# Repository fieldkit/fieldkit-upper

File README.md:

# FieldKit-*Upper*
The Upper board constitutes the thinky bits of the FieldKit system.

## Architecture
Every Fieldkit has at least three boards: Upper, Lower, and Module Base. Upper contains :

- The microcontroller.
- The OLED display and buttons.
- The real-time clock and its backup power supply.
- Flash memory for firmware.
- Separate NAND flash for data storage.
- The Micro-SD Card Slot.
- The USB Port.
- A temperature sensor.

## License Information

> *"In the long history of humankind (and animal kind, too) those who learned to collaborate and improvise most effectively have prevailed."*
>  --**Charles Darwin**

This hardware is released under **CERN Open Hardware License Version 2 - Permissive (CERN-OHL_P)**
Obviously, it's Distributed as-is; and no warranty is given.

---
*Upper was Designed by Bradley Gawthrop for FieldKit.*

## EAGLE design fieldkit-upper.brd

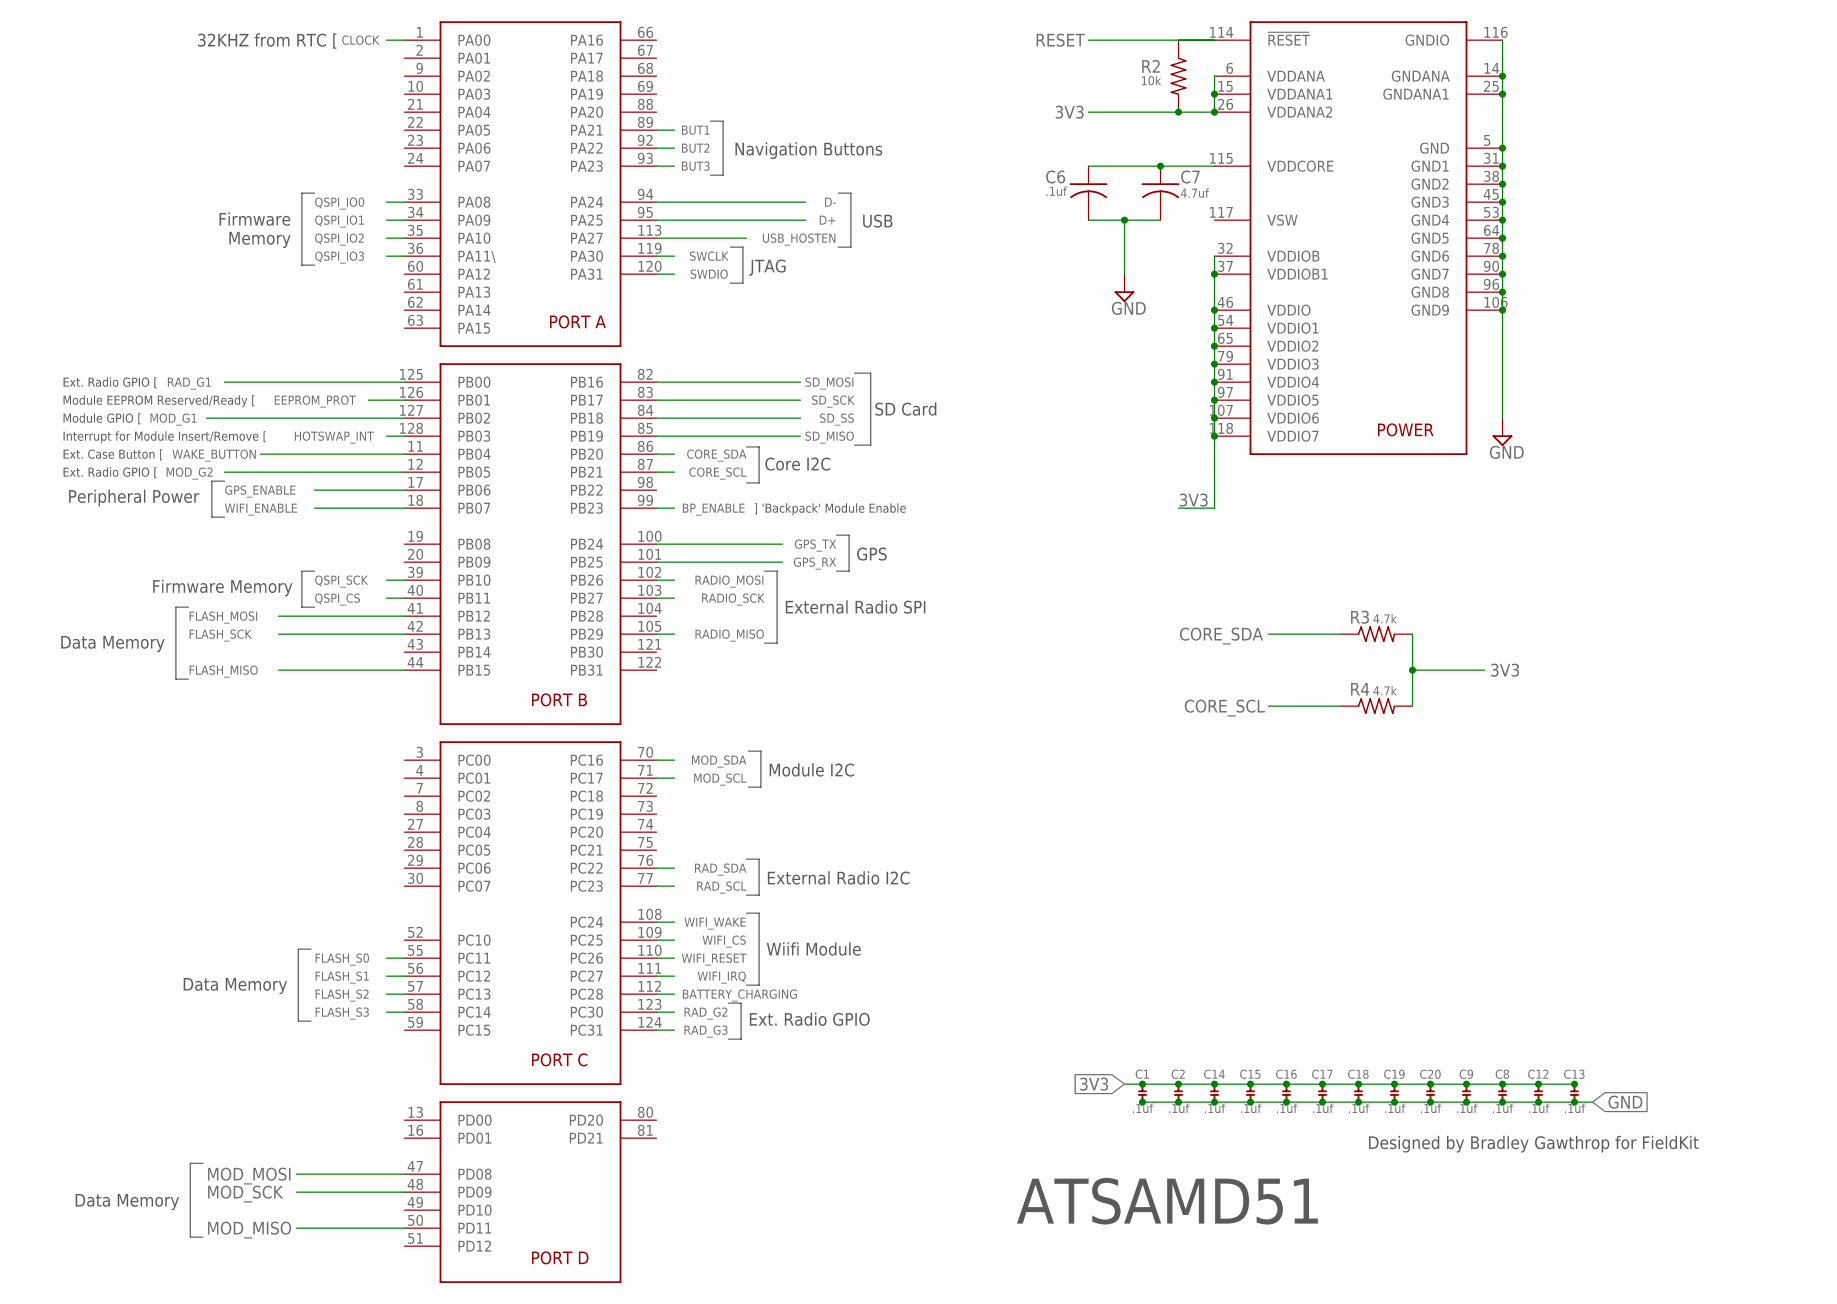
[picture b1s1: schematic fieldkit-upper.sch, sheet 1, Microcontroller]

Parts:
BRAIN: SAMD51PXXA; SQFP-S-14X14-128
C1, C2, C6, C8, C9, C12, C13, C14, C15, C16, C17, C18, C19, C20: .1uf; C0603K
C7: 4.7uf; C0603K
R2: 10k; R0603
R3, R4: 4.7k; R0603

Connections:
3V3: BRAIN.6 (VDDANA), BRAIN.15 (VDDANA1), BRAIN.26 (VDDANA2), BRAIN.32 (VDDIOB), BRAIN.37 (VDDIOB1), BRAIN.46 (VDDIO), BRAIN.54 (VDDIO1), BRAIN.65 (VDDIO2), BRAIN.79 (VDDIO3), BRAIN.91 (VDDIO4), BRAIN.97 (VDDIO5), BRAIN.107 (VDDIO6), BRAIN.118 (VDDIO7), C1.1, C2.1, C8.1, C9.1, C12.1, C13.1, C14.1, C15.1, C16.1, C17.1, C18.1, C19.1, C20.1, R2.2, R3.2, R4.2; also elsewhere on the board
BATTERY_CHARGING: BRAIN.112 (PC28); also elsewhere on the board
BP_ENABLE: BRAIN.99 (PB23); also elsewhere on the board
BUT1: BRAIN.89 (PA21); also elsewhere on the board
BUT2: BRAIN.92 (PA22); also elsewhere on the board
BUT3: BRAIN.93 (PA23); also elsewhere on the board
CLOCK: BRAIN.1 (PA00); also elsewhere on the board
CORE_SCL: BRAIN.87 (PB21), R4.1; also elsewhere on the board
CORE_SDA: BRAIN.86 (PB20), R3.1; also elsewhere on the board
D+: BRAIN.95 (PA25); also elsewhere on the board
D-: BRAIN.94 (PA24); also elsewhere on the board
EEPROM_PROT: BRAIN.126 (PB01); also elsewhere on the board
FLASH_MISO: BRAIN.44 (PB15); also elsewhere on the board
FLASH_MOSI: BRAIN.41 (PB12); also elsewhere on the board
FLASH_S0: BRAIN.55 (PC11); also elsewhere on the board
FLASH_S1: BRAIN.56 (PC12); also elsewhere on the board
FLASH_S2: BRAIN.57 (PC13); also elsewhere on the board
FLASH_S3: BRAIN.58 (PC14); also elsewhere on the board
FLASH_SCK: BRAIN.42 (PB13); also elsewhere on the board
GND: BRAIN.5 (GND), BRAIN.14 (GNDANA), BRAIN.25 (GNDANA1), BRAIN.31 (GND1), BRAIN.38 (GND2), BRAIN.45 (GND3), BRAIN.53 (GND4), BRAIN.64 (GND5), BRAIN.78 (GND6), BRAIN.90 (GND7), BRAIN.96 (GND8), BRAIN.106 (GND9), BRAIN.116 (GNDIO), C1.2, C2.2, C6.2, C7.2, C8.2, C9.2, C12.2, C13.2, C14.2, C15.2, C16.2, C17.2, C18.2, C19.2, C20.2; also elsewhere on the board
GPS_ENABLE: BRAIN.17 (PB06); also elsewhere on the board
GPS_RX: BRAIN.101 (PB25); also elsewhere on the board
GPS_TX: BRAIN.100 (PB24); also elsewhere on the board
HOTSWAP_INT: BRAIN.128 (PB03); also elsewhere on the board
MOD_G1: BRAIN.127 (PB02); also elsewhere on the board
MOD_G2: BRAIN.12 (PB05)
MOD_MISO: BRAIN.50 (PD11); also elsewhere on the board
MOD_MOSI: BRAIN.47 (PD08); also elsewhere on the board
MOD_SCK: BRAIN.48 (PD09); also elsewhere on the board
MOD_SCL: BRAIN.71 (PC17); also elsewhere on the board
MOD_SDA: BRAIN.70 (PC16); also elsewhere on the board
unnamed: BRAIN.115 (VDDCORE), C6.1, C7.1
QSPI_CS: BRAIN.40 (PB11); also elsewhere on the board
QSPI_IO0: BRAIN.33 (PA08); also elsewhere on the board
QSPI_IO1: BRAIN.34 (PA09); also elsewhere on the board
QSPI_IO2: BRAIN.35 (PA10); also elsewhere on the board
QSPI_IO3: BRAIN.36 (PA11\); also elsewhere on the board
QSPI_SCK: BRAIN.39 (PB10); also elsewhere on the board
RADIO_MISO: BRAIN.105 (PB29); also elsewhere on the board
RADIO_MOSI: BRAIN.102 (PB26); also elsewhere on the board
RADIO_SCK: BRAIN.103 (PB27); also elsewhere on the board
RAD_G1: BRAIN.125 (PB00); also elsewhere on the board
RAD_G2: BRAIN.123 (PC30); also elsewhere on the board
RAD_G3: BRAIN.124 (PC31); also elsewhere on the board
RAD_SCL: BRAIN.77 (PC23); also elsewhere on the board
RAD_SDA: BRAIN.76 (PC22); also elsewhere on the board
RESET: BRAIN.114 (!RESET), R2.1; also elsewhere on the board
SD_MISO: BRAIN.85 (PB19); also elsewhere on the board
SD_MOSI: BRAIN.82 (PB16); also elsewhere on the board
SD_SCK: BRAIN.83 (PB17); also elsewhere on the board
SD_SS: BRAIN.84 (PB18); also elsewhere on the board
SWCLK: BRAIN.119 (PA30); also elsewhere on the board
SWDIO: BRAIN.120 (PA31); also elsewhere on the board
USB_HOSTEN: BRAIN.113 (PA27)
WAKE_BUTTON: BRAIN.11 (PB04); also elsewhere on the board
WIFI_CS: BRAIN.109 (PC25); also elsewhere on the board
WIFI_ENABLE: BRAIN.18 (PB07); also elsewhere on the board
WIFI_IRQ: BRAIN.111 (PC27); also elsewhere on the board
WIFI_RESET: BRAIN.110 (PC26); also elsewhere on the board
WIFI_WAKE: BRAIN.108 (PC24); also elsewhere on the board

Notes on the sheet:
Navigation Buttons
32KHZ from RTC [
Firmware Memory
USB
JTAG
SD Card
Core I2C
External Radio SPI
] 'Backpack' Module Enable
Data Memory
Firmware Memory
Module I2C
External Radio I2C
Interrupt for Module Insert/Remove [
GPS
Ext. Radio GPIO [
Module EEPROM Reserved/Ready [
Module GPIO [
Ext. Case Button [
Peripheral Power
Wiifi Module
Ext. Radio GPIO
ATSAMD51
Designed by Bradley Gawthrop for FieldKit

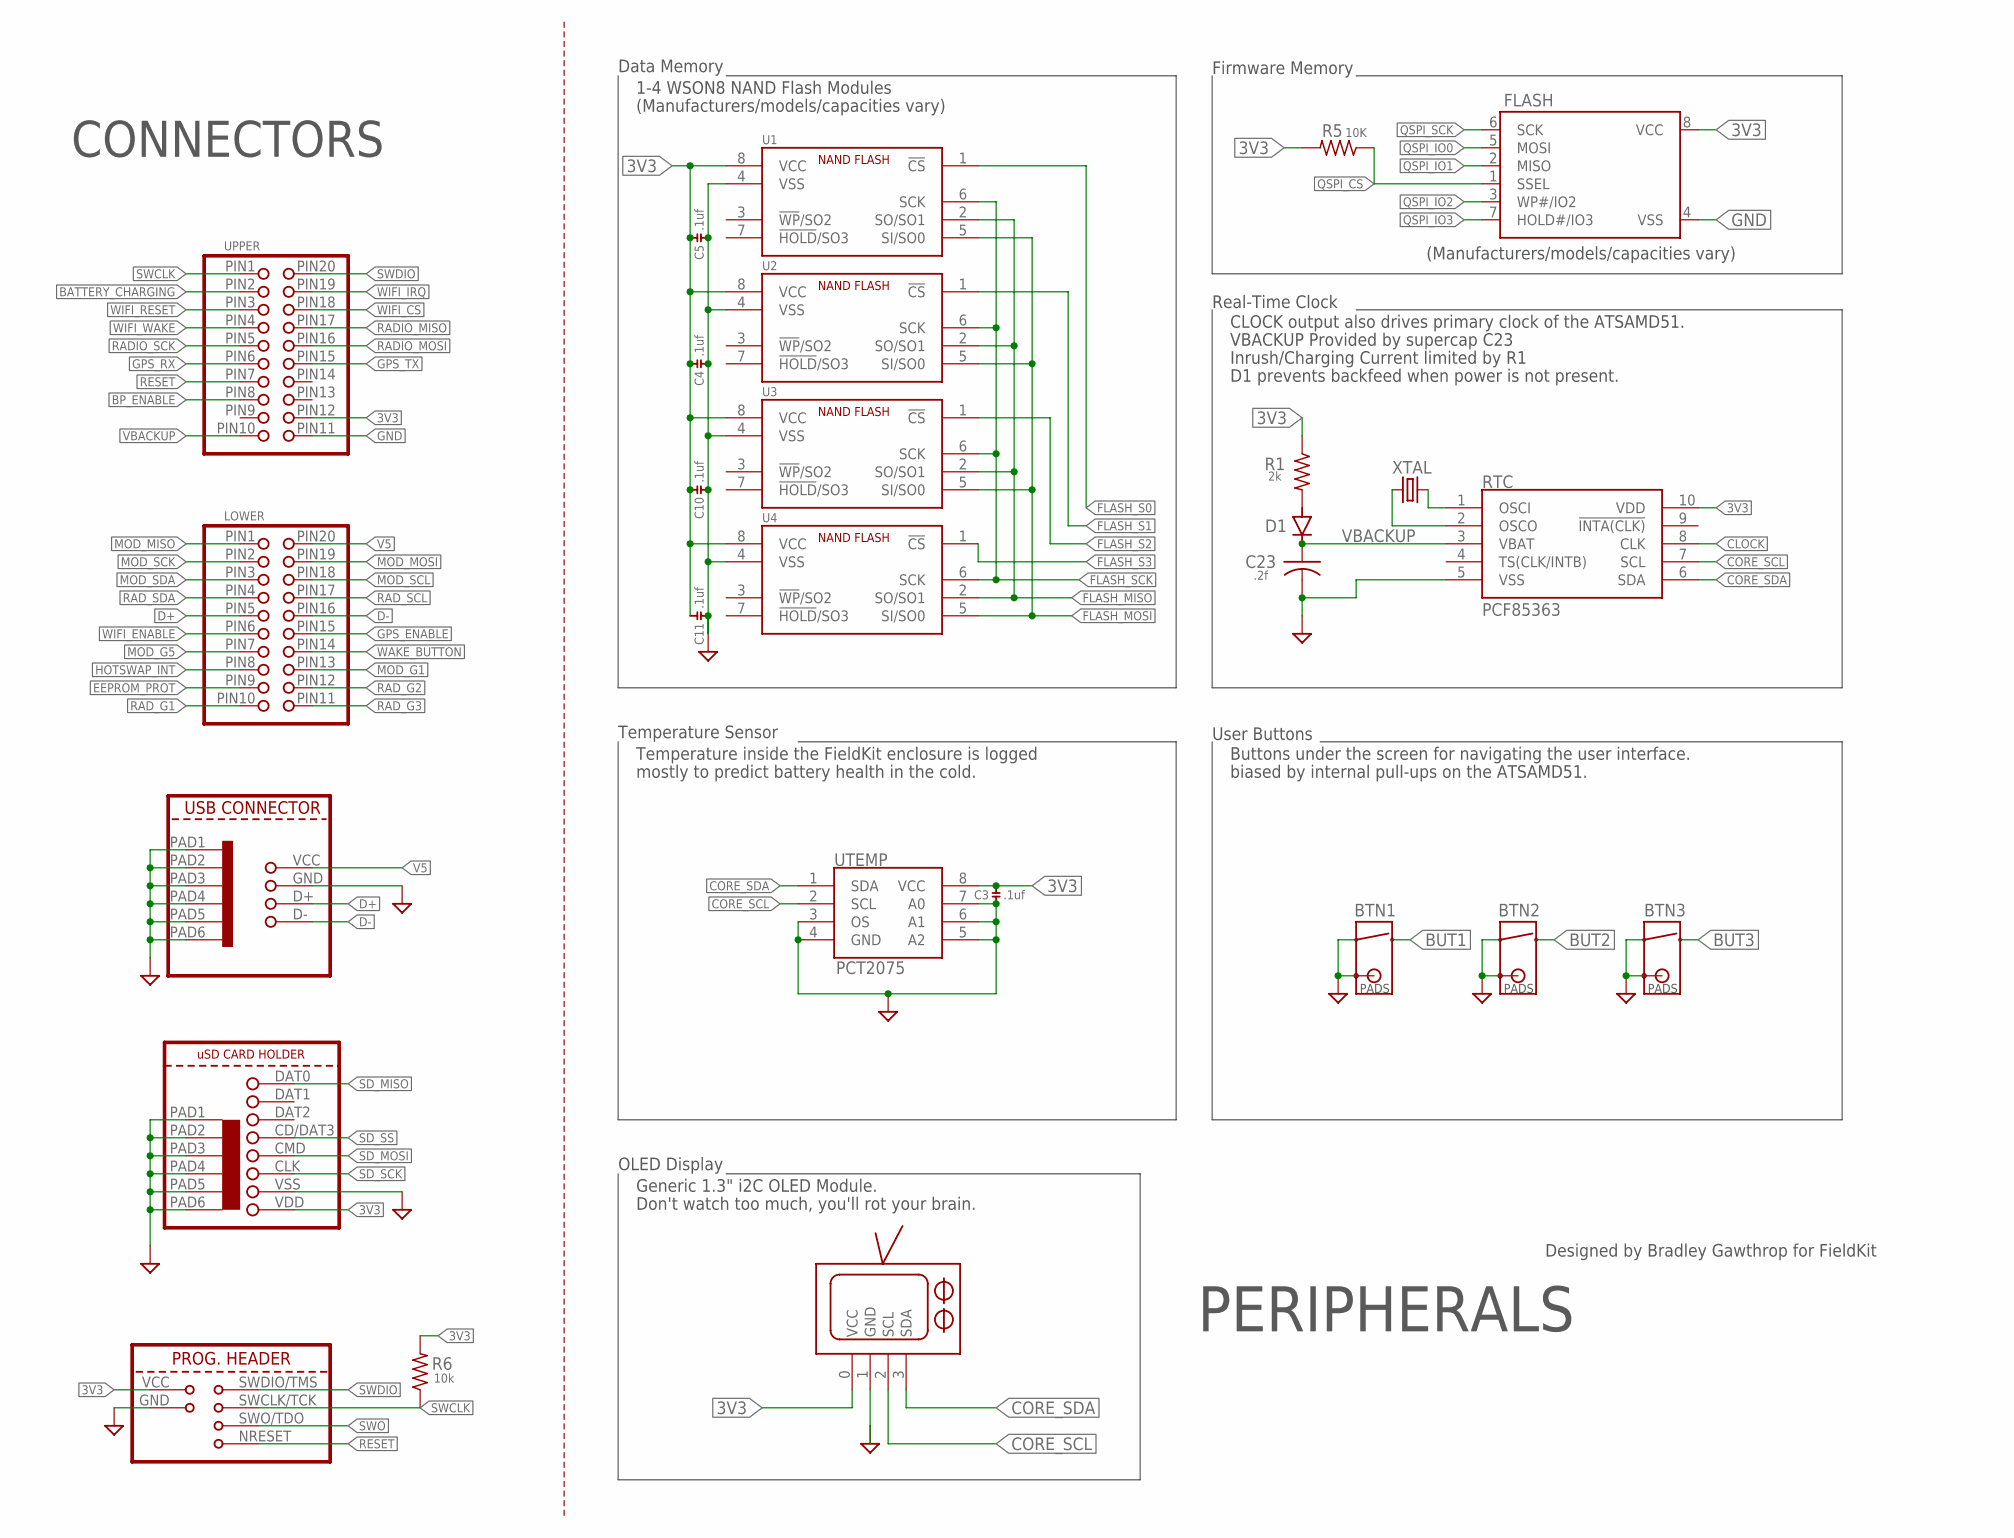
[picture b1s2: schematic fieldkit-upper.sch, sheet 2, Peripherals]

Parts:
BTN1, BTN2, BTN3: SKRTLAE010
C3, C4, C5, C10, C11: .1uf; C0603K
C23: .2f; SUPERCAP
D1: VS-10BQ015HM3/5BT; SMB
FLASH: SPIFLASH_SOIC8208MIL; SOIC8_208MIL
J1: TAG-CONNECT; TC2030-IDC
LOWER: MOLEX-15-91-2200F; 20PH-F
R1: 2k; R0603
R5: 10K; R0603
R6: 10k; R0603
RTC: PCF85363ATT; SOP50P490X110-10
SCREEN: SCREEN
SD: DM3D-SF
U1, U2, U3, U4: TC58CVG1S3HRAIG; WSON8
UPPER: MOLEX-15-91-2200F; 20PH-F
USB: MOLEX-47491-0001; MOELX-47491-0001
UTEMP: PCT2075; SO8
XTAL: ABS07W

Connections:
3V3: C3.1, C4.1, C5.1, C10.1, C11.1, FLASH.8 (VCC), J1.VCC, R1.1, R5.2, R6.2, RTC.10 (VDD), SCREEN.0 (VCC), SD.VDD, U1.8 (VCC), U2.8 (VCC), U3.8 (VCC), U4.8 (VCC), UPPER.PIN12, UTEMP.8 (VCC); also elsewhere on the board
BATTERY_CHARGING: UPPER.PIN2; also elsewhere on the board
BP_ENABLE: UPPER.PIN8; also elsewhere on the board
BUT1: BTN1.B (2); also elsewhere on the board
BUT2: BTN2.B (2); also elsewhere on the board
BUT3: BTN3.B (2); also elsewhere on the board
CLOCK: RTC.8 (CLK); also elsewhere on the board
CORE_SCL: RTC.7 (SCL), SCREEN.2 (SCL), UTEMP.2 (SCL); also elsewhere on the board
CORE_SDA: RTC.6 (SDA), SCREEN.3 (SDA), UTEMP.1 (SDA); also elsewhere on the board
D+: LOWER.PIN5, USB.D+; also elsewhere on the board
D-: LOWER.PIN16, USB.D-; also elsewhere on the board
EEPROM_PROT: LOWER.PIN9; also elsewhere on the board
FLASH_MISO: U1.2 (SO/SO1), U2.2 (SO/SO1), U3.2 (SO/SO1), U4.2 (SO/SO1); also elsewhere on the board
FLASH_MOSI: U1.5 (SI/SO0), U2.5 (SI/SO0), U3.5 (SI/SO0), U4.5 (SI/SO0); also elsewhere on the board
FLASH_S0: U1.1 (!CS); also elsewhere on the board
FLASH_S1: U2.1 (!CS); also elsewhere on the board
FLASH_S2: U3.1 (!CS); also elsewhere on the board
FLASH_S3: U4.1 (!CS); also elsewhere on the board
FLASH_SCK: U1.6 (SCK), U2.6 (SCK), U3.6 (SCK), U4.6 (SCK); also elsewhere on the board
GND: BTN1.A (1), BTN1.A2 (1), BTN1.TAB (PADS), BTN1.TAB2 (PADS), BTN2.A (1), BTN2.A2 (1), BTN2.TAB (PADS), BTN2.TAB2 (PADS), BTN3.A (1), BTN3.A2 (1), BTN3.TAB (PADS), BTN3.TAB2 (PADS), C3.2, C4.2, C5.2, C10.2, C11.2, C23.-, FLASH.4 (VSS), J1.GND, RTC.5 (VSS), SCREEN.1 (GND), SD.PAD1, SD.PAD2, SD.PAD3, SD.PAD4, SD.PAD5, SD.PAD6, SD.VSS, U1.4 (VSS), U2.4 (VSS), U3.4 (VSS), U4.4 (VSS), UPPER.PIN11, USB.GND, USB.PAD1, USB.PAD2, USB.PAD3, USB.PAD4, USB.PAD5, USB.PAD6, UTEMP.3 (OS), UTEMP.4 (GND), UTEMP.5 (A2), UTEMP.6 (A1), UTEMP.7 (A0); also elsewhere on the board
GPS_ENABLE: LOWER.PIN15; also elsewhere on the board
GPS_RX: UPPER.PIN6; also elsewhere on the board
GPS_TX: UPPER.PIN15; also elsewhere on the board
HOTSWAP_INT: LOWER.PIN8; also elsewhere on the board
MOD_G1: LOWER.PIN13; also elsewhere on the board
MOD_G5: LOWER.PIN7
MOD_MISO: LOWER.PIN1; also elsewhere on the board
MOD_MOSI: LOWER.PIN19; also elsewhere on the board
MOD_SCK: LOWER.PIN2; also elsewhere on the board
MOD_SCL: LOWER.PIN18; also elsewhere on the board
MOD_SDA: LOWER.PIN3; also elsewhere on the board
unnamed: D1.A, R1.2
unnamed: RTC.1 (OSCI), XTAL.P$2 (2)
unnamed: RTC.2 (OSCO), XTAL.P$1 (1)
QSPI_CS: FLASH.1 (SSEL), R5.1; also elsewhere on the board
QSPI_IO0: FLASH.5 (MOSI); also elsewhere on the board
QSPI_IO1: FLASH.2 (MISO); also elsewhere on the board
QSPI_IO2: FLASH.3 (WP#/IO2); also elsewhere on the board
QSPI_IO3: FLASH.7 (HOLD#/IO3); also elsewhere on the board
QSPI_SCK: FLASH.6 (SCK); also elsewhere on the board
RADIO_MISO: UPPER.PIN17; also elsewhere on the board
RADIO_MOSI: UPPER.PIN16; also elsewhere on the board
RADIO_SCK: UPPER.PIN5; also elsewhere on the board
RAD_G1: LOWER.PIN10; also elsewhere on the board
RAD_G2: LOWER.PIN12; also elsewhere on the board
RAD_G3: LOWER.PIN11; also elsewhere on the board
RAD_SCL: LOWER.PIN17; also elsewhere on the board
RAD_SDA: LOWER.PIN4; also elsewhere on the board
RESET: J1.NRESET (RESET), UPPER.PIN7; also elsewhere on the board
SD_MISO: SD.DAT0; also elsewhere on the board
SD_MOSI: SD.CMD; also elsewhere on the board
SD_SCK: SD.CLK; also elsewhere on the board
SD_SS: SD.CD/DAT3 (DAT3); also elsewhere on the board
SWCLK: J1.SWCLK/TCK (SWCLK), R6.1, UPPER.PIN1; also elsewhere on the board
SWDIO: J1.SWDIO/TMS (SWDIO), UPPER.PIN20; also elsewhere on the board
SWO: J1.SWO/TDO (SWO)
V5: LOWER.PIN20, USB.VCC (VBUS)
VBACKUP: C23.+, D1.C, RTC.3 (VBAT), UPPER.PIN10
WAKE_BUTTON: LOWER.PIN14; also elsewhere on the board
WIFI_CS: UPPER.PIN18; also elsewhere on the board
WIFI_ENABLE: LOWER.PIN6; also elsewhere on the board
WIFI_IRQ: UPPER.PIN19; also elsewhere on the board
WIFI_RESET: UPPER.PIN3; also elsewhere on the board
WIFI_WAKE: UPPER.PIN4; also elsewhere on the board

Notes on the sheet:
.2f
CONNECTORS
Data Memory
1-4 WSON8 NAND Flash Modules
(Manufacturers/models/capacities vary)
Firmware Memory
Real-Time Clock
CLOCK output also drives primary clock of the ATSAMD51.
VBACKUP Provided by supercap C23
Inrush/Charging Current limited by R1
D1 prevents backfeed when power is not present.
RTC
PCF85363
Temperature Sensor
Temperature inside the FieldKit enclosure is logged
mostly to predict battery health in the cold.
User Buttons
Buttons under the screen for navigating the user interface.
biased by internal pull-ups on the ATSAMD51.
OLED Display
Generic 1.3" i2C OLED Module.
Don't watch too much, you'll rot your brain.
PERIPHERALS
Designed by Bradley Gawthrop for FieldKit

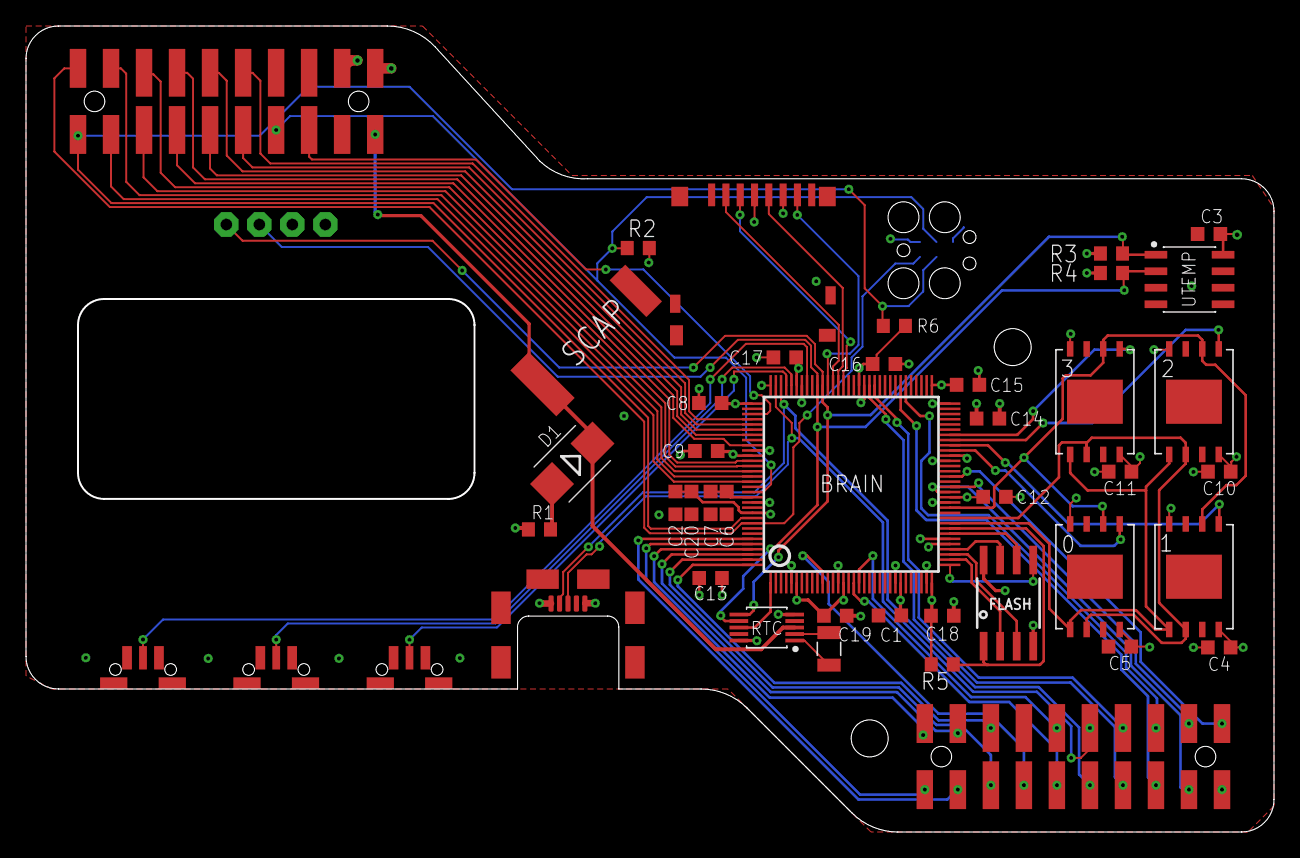
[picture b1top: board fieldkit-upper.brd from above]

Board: 4 copper layers, 95.8 x 61.8 mm, 46 parts (1 on the bottom side), 63 nets.

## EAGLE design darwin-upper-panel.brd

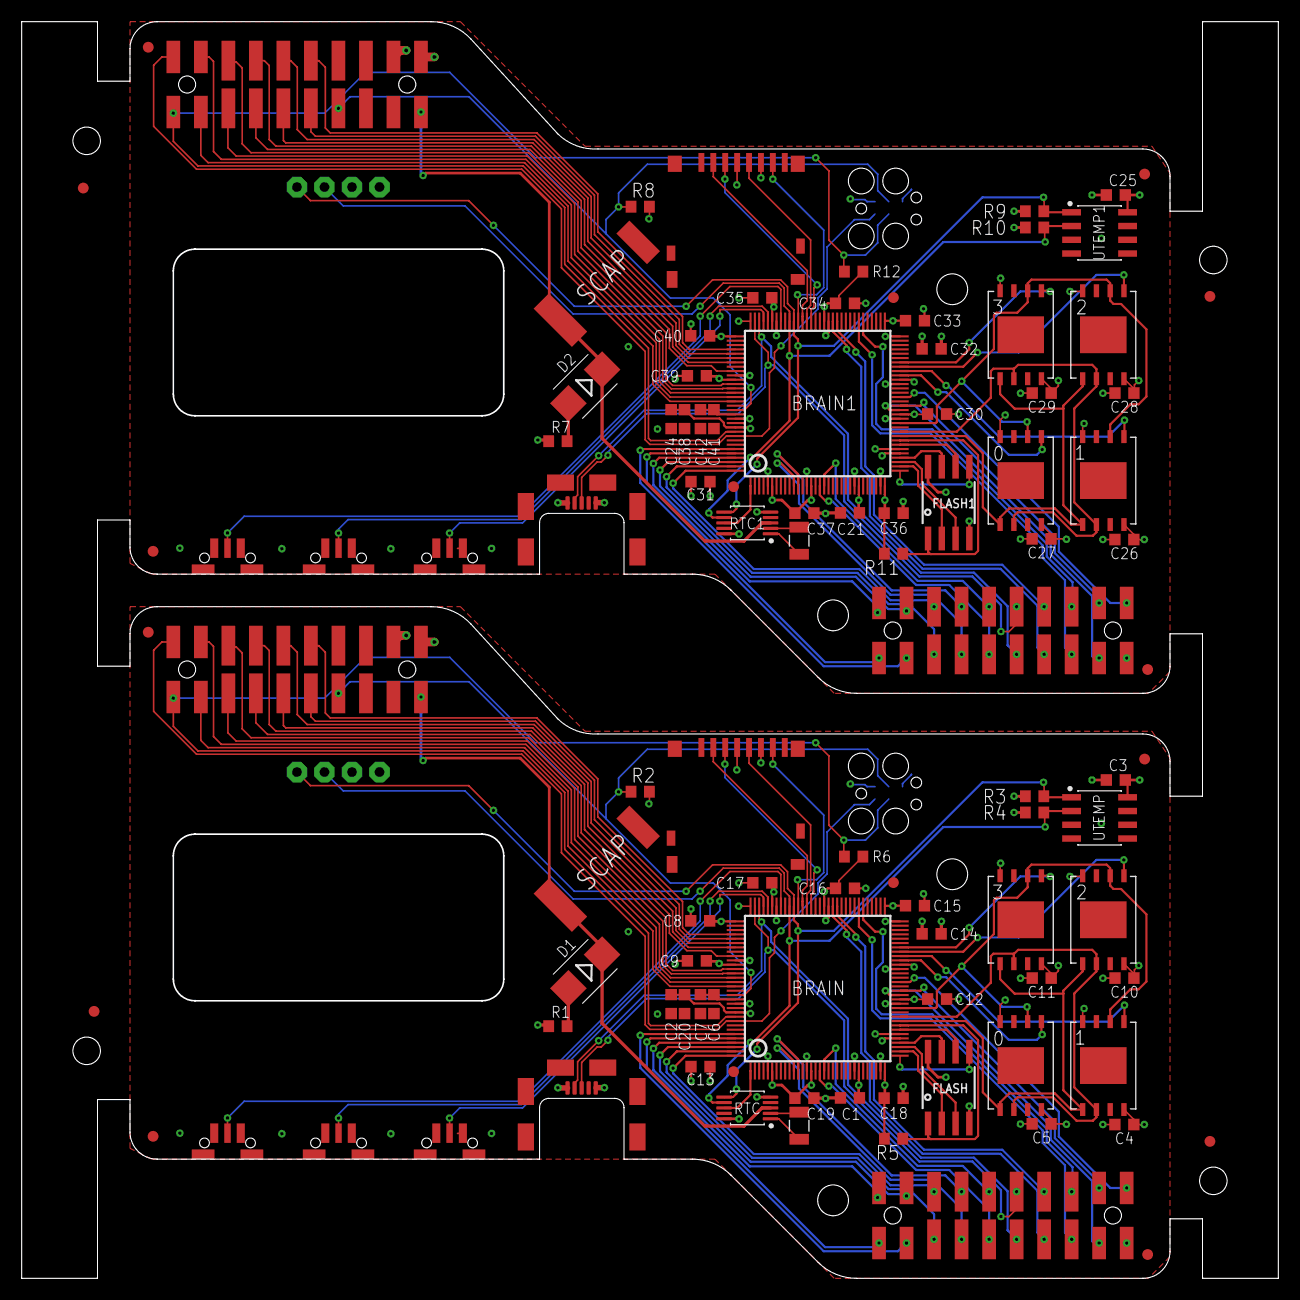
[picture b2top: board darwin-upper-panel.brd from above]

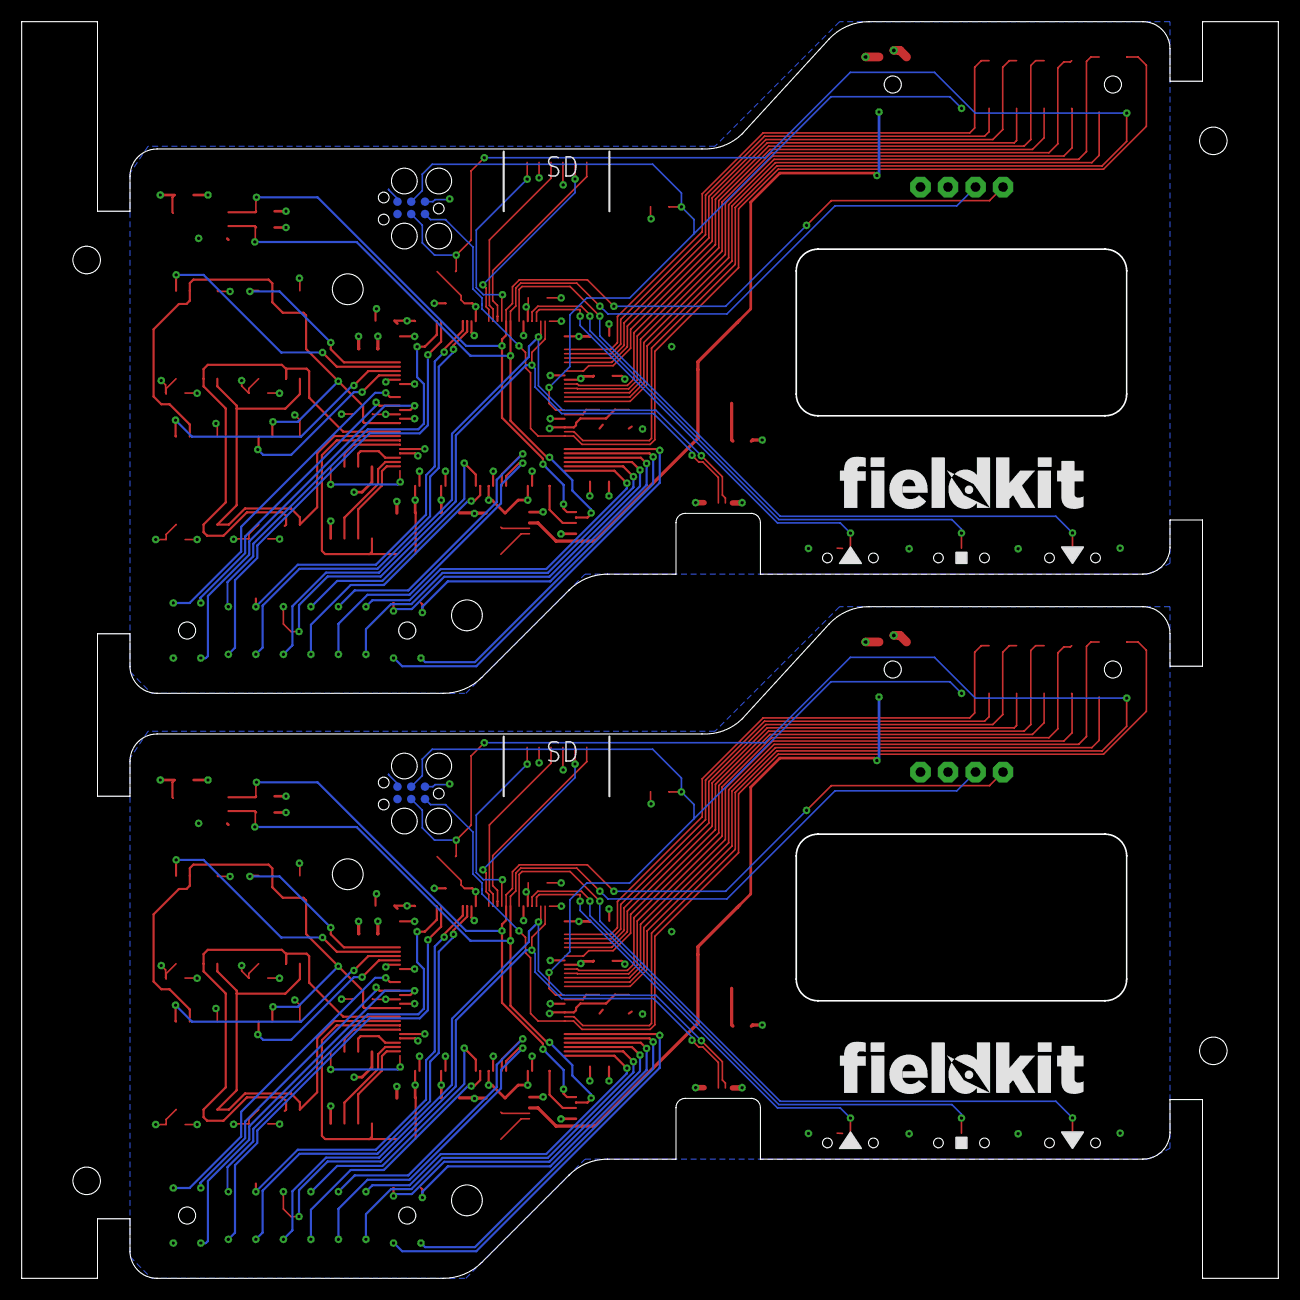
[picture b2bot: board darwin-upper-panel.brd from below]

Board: 4 copper layers, 115.8 x 115.8 mm, 108 parts (2 on the bottom side), 126 nets.

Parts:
BRAIN, BRAIN1: SAMD51PXXA; SQFP-S-14X14-128
BTN1, BTN2, BTN3, BTN4, BTN5, BTN6: SKRTLAE010
C1, C2, C3, C4, C5, C6, C8, C9, C10, C11, C12, C13, C14, C15, C16, C17, C18, C19, C20, C21, C24, C25, C26, C27, C28, C29, C30, C31, C32, C33, C34, C35, C36, C37, C38, C39, C40, C41: .1uf; C0603K
C7, C42: 4.7uf; C0603K
C22, C23: .2f; SUPERCAP
D1, D2: VS-10BQ015HM3/5BT; SMB
FID1, FID2, FID3, FID4, FID5, FID6, FID7, FID8, FID9, FID10, FID11, FID12, FID13, FID14, FID15, FID16: FIDUCIAL_1MM
FLASH, FLASH1: SOIC8_208MIL
J1, J2: TAG-CONNECT; TC2030-IDC
LOWER, LOWER1: MOLEX-15-91-2200F; 20PH-F
R1, R7: 2k; R0603
R2, R6, R8, R12: 10k; R0603
R3, R4, R9, R10: 4.7k; R0603
R5, R11: 10K; R0603
RTC, RTC1: PCF85363ATT; SOP50P490X110-10
SCREEN, SCREEN1: SCREEN
SD, SD1: DM3D-SF
U1, U2, U3, U4, U5, U6, U7, U8: TC58CVG1S3HRAIG; WSON8
U$1, U$14: ABS07W
UPPER, UPPER1: MOLEX-15-91-2200F; 20PH-F
USB, USB1: MOLEX-47491-0001; MOELX-47491-0001
UTEMP, UTEMP1: PCT2075; SO8

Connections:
3V1: BRAIN1.6, BRAIN1.15, BRAIN1.26, BRAIN1.32, BRAIN1.37, BRAIN1.46, BRAIN1.54, BRAIN1.65, BRAIN1.79, BRAIN1.91, BRAIN1.97, BRAIN1.107, BRAIN1.118, C21.1, C24.1, C25.1, C26.1, C27.1, C28.1, C29.1, C30.1, C31.1, C32.1, C33.1, C34.1, C35.1, C36.1, C37.1, C38.1, C39.1, C40.1, FLASH1.8, J2.VCC, R7.1, R8.2, R9.2, R10.2, R11.2, R12.2, RTC1.10, SCREEN1.P0, SD1.VDD, U5.P$8, U6.P$8, U7.P$8, U8.P$8, UPPER1.PIN12, UTEMP1.8
3V3: BRAIN.6, BRAIN.15, BRAIN.26, BRAIN.32, BRAIN.37, BRAIN.46, BRAIN.54, BRAIN.65, BRAIN.79, BRAIN.91, BRAIN.97, BRAIN.107, BRAIN.118, C1.1, C2.1, C3.1, C4.1, C5.1, C8.1, C9.1, C10.1, C11.1, C12.1, C13.1, C14.1, C15.1, C16.1, C17.1, C18.1, C19.1, C20.1, FLASH.8, J1.VCC, R1.1, R2.2, R3.2, R4.2, R5.2, R6.2, RTC.10, SCREEN.P0, SD.VDD, U1.P$8, U2.P$8, U3.P$8, U4.P$8, UPPER.PIN12, UTEMP.8
BUT1: BRAIN.89, BTN1.B
BUT2: BRAIN.92, BTN2.B
BUT3: BRAIN.93, BTN3.B
BUT4: BRAIN1.89, BTN4.B
BUT5: BRAIN1.92, BTN5.B
BUT6: BRAIN1.93, BTN6.B
CLOCK: BRAIN.1, RTC.8
CLOCK1: BRAIN1.1, RTC1.8
CORE_SCL: BRAIN.87, R4.1, RTC.7, SCREEN.P2, UTEMP.2
CORE_SCL1: BRAIN1.87, R10.1, RTC1.7, SCREEN1.P2, UTEMP1.2
CORE_SDA: BRAIN.86, R3.1, RTC.6, SCREEN.P3, UTEMP.1
CORE_SDA1: BRAIN1.86, R9.1, RTC1.6, SCREEN1.P3, UTEMP1.1
D+: BRAIN.95, LOWER.PIN5, USB.D+
D+1: BRAIN1.95, LOWER1.PIN5, USB1.D+
D-: BRAIN.94, LOWER.PIN16, USB.D-
D-1: BRAIN1.94, LOWER1.PIN16, USB1.D-
EEPROM_PROT: BRAIN.126, LOWER.PIN9
EEPROM_PROT1: BRAIN1.126, LOWER1.PIN9
FLASH_MISO: BRAIN.44, U1.P$2, U2.P$2, U3.P$2, U4.P$2
FLASH_MISO1: BRAIN1.44, U5.P$2, U6.P$2, U7.P$2, U8.P$2
FLASH_MOSI: BRAIN.41, U1.P$5, U2.P$5, U3.P$5, U4.P$5
FLASH_MOSI1: BRAIN1.41, U5.P$5, U6.P$5, U7.P$5, U8.P$5
FLASH_S0: BRAIN.55, U1.P$1
FLASH_S1: BRAIN.56, U2.P$1
FLASH_S2: BRAIN.57, U3.P$1
FLASH_S3: BRAIN.58, U4.P$1
FLASH_S4: BRAIN1.55, U5.P$1
FLASH_S5: BRAIN1.56, U6.P$1
FLASH_S6: BRAIN1.57, U7.P$1
FLASH_S7: BRAIN1.58, U8.P$1
FLASH_SCK: BRAIN.42, U1.P$6, U2.P$6, U3.P$6, U4.P$6
FLASH_SCK1: BRAIN1.42, U5.P$6, U6.P$6, U7.P$6, U8.P$6
GND: BRAIN.5, BRAIN.14, BRAIN.25, BRAIN.31, BRAIN.38, BRAIN.45, BRAIN.53, BRAIN.64, BRAIN.78, BRAIN.90, BRAIN.96, BRAIN.106, BRAIN.116, BTN1.A, BTN1.A2, BTN1.TAB, BTN1.TAB2, BTN2.A, BTN2.A2, BTN2.TAB, BTN2.TAB2, BTN3.A, BTN3.A2, BTN3.TAB, BTN3.TAB2, C1.2, C2.2, C3.2, C4.2, C5.2, C6.2, C7.2, C8.2, C9.2, C10.2, C11.2, C12.2, C13.2, C14.2, C15.2, C16.2, C17.2, C18.2, C19.2, C20.2, C23.-, FLASH.4, J1.GND, RTC.5, SCREEN.P1, SD.VSS, U1.P$4, U2.P$4, U3.P$4, U4.P$4, UPPER.PIN11, USB.GND, UTEMP.3, UTEMP.4, UTEMP.5, UTEMP.6, UTEMP.7
GND1: BRAIN1.5, BRAIN1.14, BRAIN1.25, BRAIN1.31, BRAIN1.38, BRAIN1.45, BRAIN1.53, BRAIN1.64, BRAIN1.78, BRAIN1.90, BRAIN1.96, BRAIN1.106, BRAIN1.116, BTN4.A, BTN4.A2, BTN4.TAB, BTN4.TAB2, BTN5.A, BTN5.A2, BTN5.TAB, BTN5.TAB2, BTN6.A, BTN6.A2, BTN6.TAB, BTN6.TAB2, C21.2, C22.-, C24.2, C25.2, C26.2, C27.2, C28.2, C29.2, C30.2, C31.2, C32.2, C33.2, C34.2, C35.2, C36.2, C37.2, C38.2, C39.2, C40.2, C41.2, C42.2, FLASH1.4, J2.GND, RTC1.5, SCREEN1.P1, SD1.VSS, U5.P$4, U6.P$4, U7.P$4, U8.P$4, UPPER1.PIN11, USB1.GND, UTEMP1.3, UTEMP1.4, UTEMP1.5, UTEMP1.6, UTEMP1.7
GPS_RX: BRAIN.101, UPPER.PIN6
GPS_RX1: BRAIN1.101, UPPER1.PIN6
GPS_TX: BRAIN.100, UPPER.PIN15
GPS_TX1: BRAIN1.100, UPPER1.PIN15
HOTSWAP_INT: BRAIN.128, LOWER.PIN8
HOTSWAP_INT1: BRAIN1.128, LOWER1.PIN8
MOD_G0: BRAIN.125, LOWER.PIN10
MOD_G1: BRAIN1.125, LOWER1.PIN10
MOD_G2: BRAIN.127, LOWER.PIN13
MOD_G3: BRAIN1.127, LOWER1.PIN13
MOD_G4: BRAIN.11, LOWER.PIN14
MOD_G5: BRAIN.12, LOWER.PIN7
MOD_G6: BRAIN.17, LOWER.PIN15
MOD_G7: BRAIN.18, LOWER.PIN6
MOD_G8: BRAIN.108, UPPER.PIN4
MOD_G9: BRAIN.109, UPPER.PIN18
MOD_G10: BRAIN.110, UPPER.PIN3
MOD_G11: BRAIN.111, UPPER.PIN19
MOD_G12: BRAIN.112, UPPER.PIN2
MOD_G13: BRAIN.123, LOWER.PIN12
MOD_G14: BRAIN.124, LOWER.PIN11
MOD_G15: BRAIN1.11, LOWER1.PIN14
MOD_G16: BRAIN1.12, LOWER1.PIN7
MOD_G17: BRAIN1.17, LOWER1.PIN15
MOD_G18: BRAIN1.18, LOWER1.PIN6
MOD_G19: BRAIN1.108, UPPER1.PIN4
MOD_G20: BRAIN1.109, UPPER1.PIN18
MOD_G21: BRAIN1.110, UPPER1.PIN3
MOD_G22: BRAIN1.111, UPPER1.PIN19
MOD_G23: BRAIN1.112, UPPER1.PIN2
MOD_G24: BRAIN1.123, LOWER1.PIN12
MOD_G25: BRAIN1.124, LOWER1.PIN11
MOD_MISO: BRAIN.50, LOWER.PIN1
MOD_MISO1: BRAIN1.50, LOWER1.PIN1
MOD_MOSI: BRAIN.47, LOWER.PIN19
MOD_MOSI1: BRAIN1.47, LOWER1.PIN19
MOD_SCK: BRAIN.48, LOWER.PIN2
MOD_SCK1: BRAIN1.48, LOWER1.PIN2
MOD_SCL: BRAIN.71, LOWER.PIN18
MOD_SCL1: BRAIN1.71, LOWER1.PIN18
MOD_SDA: BRAIN.70, LOWER.PIN3
MOD_SDA1: BRAIN1.70, LOWER1.PIN3
unnamed: D2.A, R7.2
unnamed: D1.A, R1.2
unnamed: RTC.1, U$14.P$2
unnamed: RTC.2, U$14.P$1
unnamed: RTC1.1, U$1.P$2
unnamed: BRAIN.115, C6.1, C7.1
unnamed: RTC1.2, U$1.P$1
unnamed: BRAIN1.115, C41.1, C42.1
QSPI_CS: BRAIN.40, FLASH.1, R5.1
QSPI_CS1: BRAIN1.40, FLASH1.1, R11.1
QSPI_IO0: BRAIN.33, FLASH.5
QSPI_IO1: BRAIN.34, FLASH.2
QSPI_IO2: BRAIN.35, FLASH.3
QSPI_IO3: BRAIN.36, FLASH.7
QSPI_IO4: BRAIN1.33, FLASH1.5
QSPI_IO5: BRAIN1.34, FLASH1.2
QSPI_IO6: BRAIN1.35, FLASH1.3
QSPI_IO7: BRAIN1.36, FLASH1.7
QSPI_SCK: BRAIN.39, FLASH.6
QSPI_SCK1: BRAIN1.39, FLASH1.6
RADIO_MISO: BRAIN.105, UPPER.PIN17
RADIO_MISO1: BRAIN1.105, UPPER1.PIN17
RADIO_MOSI: BRAIN.102, UPPER.PIN16
RADIO_MOSI1: BRAIN1.102, UPPER1.PIN16
RADIO_SCK: BRAIN.103, UPPER.PIN5
RADIO_SCK1: BRAIN1.103, UPPER1.PIN5
RAD_SCL: BRAIN.77, LOWER.PIN17
RAD_SCL1: BRAIN1.77, LOWER1.PIN17
RAD_SDA: BRAIN.76, LOWER.PIN4
RAD_SDA1: BRAIN1.76, LOWER1.PIN4
RESET: BRAIN.114, J1.NRESET, R2.1, UPPER.PIN7
RESET1: BRAIN1.114, J2.NRESET, R8.1, UPPER1.PIN7
SD_MISO: BRAIN.85, SD.DAT0
SD_MISO1: BRAIN1.85, SD1.DAT0
SD_MOSI: BRAIN.82, SD.CMD
SD_MOSI1: BRAIN1.82, SD1.CMD
SD_SCK: BRAIN.83, SD.CLK
SD_SCK1: BRAIN1.83, SD1.CLK
SD_SS: BRAIN.84, SD.CD/DAT3
SD_SS1: BRAIN1.84, SD1.CD/DAT3
SWCLK: BRAIN.119, J1.SWCLK/TCK, R6.1, UPPER.PIN1
SWCLK1: BRAIN1.119, J2.SWCLK/TCK, R12.1, UPPER1.PIN1
SWDIO: BRAIN.120, J1.SWDIO/TMS, UPPER.PIN20
SWDIO1: BRAIN1.120, J2.SWDIO/TMS, UPPER1.PIN20
V1: LOWER1.PIN20, USB1.VCC
V5: LOWER.PIN20, USB.VCC
VBACKUP: C23.+, D1.C, RTC.3, UPPER.PIN10
VBACKUP1: C22.+, D2.C, RTC1.3, UPPER1.PIN10

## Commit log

2019-05-23 Initial Lash-Up.
2019-05-23 DRC related cleanup.
2019-05-23 Silk cleanup and other housecleaning.
2019-05-23 Added screen contacts
2019-05-23 Routing Tweaks
2019-05-23 Minor cleanup, CAM files created.
2019-06-13 Corrected VDDCORE and VSW errors.
2019-06-13 Cache file cleanup.
2019-06-13 Added pullup resistor for QSPI Flash chip select.
2019-06-13 Moved SD card, USB, and Temp sensor posistions for better cable access. Expanded screen window by 2MM.
2019-06-14 Fixed Memory footprints. CAM output for TA2. Reorganized CAM files.
2019-06-14 Whoops! Fixed a DRC errors. Re-CAM'd as TA2b.
2019-07-17 Fixed SD Power Disconnect.
2019-09-03 Panelized. PA1.
2019-09-30 Cleanup.
2020-01-16 Moved USB connector location, replaced buttons, tidied decoupling caps and routing.
2020-02-11 Added Tag-Connect header.
2020-05-01 Schematic cleanup and add PDF.
2021-02-13 Schematic readability overhaul, repo look & feel.
2021-02-13 Minor schematic style changes.
2021-02-14 Updated exclusions.
2021-06-08 Routing cleanup, pin nomenclature fixes.
